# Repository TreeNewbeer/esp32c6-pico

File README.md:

# ESP32-C6 Pico · Rev A

2026-09-11 第一版 PCB 提交快照：保留用户在居中后对 R19、R15、局部短线及图形的继续调整；R19 / R15 当前坐标为 (115.70, 120.40) / (115.70, 122.36) mm。已重新填铜并同步贴装坐标、二维预览和报告，**ERC 0、DRC 错误 0 / 丝印警告 1、未连接 0、一致性问题 0，QA 39/53**。见 [当前提交记录](output/first-pcb-revision.json)。以下居中对比及旧 3D 图保留为历史记录。

2026-09-10 最新 PCB 微调：以用户已基本完成的第一版 layout 为输入，USB 向右 1.00 mm、两颗按键各向右 0.50 mm，均对齐板框中心 X=110.00 mm；按键间距及纵向位置不变，RST / BOOT 文字跟随移动，D2 位号丝印隐藏。为避让孔位及器件庭院，D4 向右 0.20 mm / 向下 0.10 mm、R15 向右 0.50 mm，局部修整短线；其余器件位置及板框、射频、晶振、禁布区不变。原理图和电路网络未改动，过孔仍为 89 个。重新填铜后 **ERC 0、DRC 错误 0、未连接 0、一致性 0**，保留输入已有的 1 项板头丝印警告；**QA 39/53，无新增失败项**。贴装坐标、二维预览和当前原理图导出的网表已更新，旧 3D 图为历史记录。见 [修改记录](output/usb-buttons-centered.json) 与 [前后对比](output/usb-buttons-centered-comparison.png)；以下先前轮次的数据仅作历史参考。

2026-09-10 最新（仅原理图）：RGB 控制已由 GPIO21 切回 **GPIO8（U1.14，与 J2.7 共用）**，GPIO21（U1.34）标记不连接。已按用户确认对齐官方 DevKitC-1 v1.4：**R9 = 3.3 kΩ 将 GPIO8 上拉到 3.3 V，R19 = 10 kΩ 将二极管阳极侧数据节点上拉到 5 V，R15 = 0 Ω 串联接入 DIN**。保留两颗上拉，D6 阴极朝 GPIO8；R9 / R15 的阻值、BOM 和检查条件均已同步。ERC 0，主控外围实线检查全部通过。PCB、布局和贴装坐标未修改，尚未同步这次 GPIO8 变更；既有 DRC / QA 报告不是新原理图的一致性验证。最新网表、BOM 和两页预览已更新；设计清单同时修正输入原理图已有的 J3 脚序及 D2 封装字段偏差，未改动这些电路。见 [GPIO8 原理图记录](output/rgb-gpio8-schematic.json) 与 [RGB 局部预览](output/schematic/rgb-gpio8.png)。

以下布局轮次和检查数字为历史记录；当前原理图与 PCB 的同步状态以上述说明为准。

当前 PCB 为 **18.0 × 29.0 mm、四层、标称 0.8 mm**，使用 ESP32-C6 QFN40、4 MB 外置 Flash、横向陶瓷天线与原生 USB Serial/JTAG。已按最新原理图移除 USB 的 R12、R13、C27、C28 并完成 USB 直连布线；RGB 灯改用二极管加 5 V 上拉驱动，不再使用电平转换芯片。

2026-09-10 此前 RGB 驱动同步：**按官方 ESP32-C6-DevKitC-1 v1.4 的方式，用 D6（1N4148WS / SOD-323）+ R19（10 kΩ 上拉到 USB 5 V）替换 SN74LV1T125 电平转换器**，删除 U4、其去耦 C26 和 GPIO21 下拉 R16；R15 = 330 Ω 移到 D2 的 DIN 焊盘旁，原来绕过 D2 的数据绕线一并删除。庭院净省约 10 mm²，背面原缓冲器口袋基本腾空，少一个 IC 料号。电平按二极管压降核算（高电平约 3.9 V > 0.7 × VDD，低电平约 0.7 V < 0.3 × VDD，10 kΩ 上拉上升沿约 105 ns），**尚未上电或用示波器实测**。范围、基线对比与哈希见 [RGB 二极管驱动记录](output/rgb-diode-drive.json)，局部对比见 [改动前后对比图](output/rgb-diode-comparison.png)。

2026-09-10 此前 USB 同步：**删除 R12 / R13（22 Ω 串阻）和 C27 / C28（选装电容）**，U1.18 / U1.19 直接连接 USB_D− / USB_D+；保留 USB-C、CC 下拉及 D4 静电保护。清除两条电容支路及其过孔，简化主控附近走线；保持 0.15 mm 线宽、每根数据线两次换层，不增加蛇形补偿。

当前 **59 个器件位、55 个默认装配；ERC 0、原理图一致性 0**。PCB 仍处在重排右排针（J3）的过程中，**DRC 5 项违规、9 项未连接、QA 45/53**：既有的 MCU 7/9 个中心地孔两项检查、匹配网络共轴、天线/晶振间距，加上尚未连上的 7 条 J3 网络、3 个未盖油过孔和 R14 旁一处 +3V3 间距。这些项与 RGB 改动前的同一工程基线（DRC 5、未连接 9、QA 44/52）逐项一致，本轮没有新增违规，但**投板前必须先完成 J3 布线并清零**。除本轮 RGB 三件外，其余器件的位置、角度、安装面和封装不变；BOM、坐标、原理图和 PCB 预览已更新，详见 [RGB 二极管驱动记录](output/rgb-diode-drive.json) 与 [USB 同步记录](output/usb-layout-sync.json)。尚未进行实板 USB、RGB 或射频验证。

以下引脚同步及布局调整记录为历史状态；当前器件数、USB 与 RGB 电路以上面两段为准。

2026-09-10 此前引脚同步：**J2 / J3 全部 24 个脚位已按用户修改的原理图更新，信号、电源和接地均已连通，包括 GPIO5（U1.11 → J2.4）**。左列从板头依次为 GPIO2–GPIO11、3V3、GND；右列为 GPIO1、GPIO0、GPIO15、TX、RX、GPIO18、GPIO19、GPIO20、GPIO22、GPIO23、5V、GND。背面功能丝印、设计清单、原理图预览及 PCB 预览已同步。

**全部 64 个器件的位置、角度、安装面、封装和装配状态均保持输入状态**；板框、logo、禁布区，以及 RF、晶振、USB、Flash 等非排针网络的原有铜线几何保持不变。重排排针支路，同时接回输入板已断开的 C8/C9/C10 3V3 支路，恢复 64 个器件的原理图关联路径。为分隔的表层地铜补充四颗接地过孔，Y1.2 最近地孔距离改善为 0.65 mm；另将一颗原有 VBUS_USB 过孔明确设置为双面盖油。过孔从本次实际输入的 122 颗变为 130 颗。

当前 **ERC 0、DRC 违规 0、未连接 0、原理图一致性 0；独立 QA 48/52**。没有新增失败项；保留四项既有失败：MCU 中心地孔仍为 7/9（两项检查）、天线匹配器件共轴及天线/晶振 8.5 mm 间距目标。最新报告与输入基线见 [引脚同步记录](output/pin-layout-sync.json)；尚未进行实板或射频验证。以下收窄记录属于本轮之前的历史状态，旧脚位和 GPIO5 待连状态以本段及下方接口表为准。

2026-09-10 左侧收窄：板框现为 **18.0 × 29.0 mm**，左板边与 J2 同步右移 **2.00 mm（四个 0.50 mm 步长）**，面积由 580 降至 522 mm²，减少 10%。J2 / J3 中心 X 为 102.25 / 117.75 mm，列中心距 15.50 mm；针距仍为 2.00 mm，焊盘铜到两侧板边仍各 0.575 mm。为避让左排针，仅另调整背面的 C8、C28、R8，其他 60 个器件保持位置、安装面和封装，L2、RF/晶振走线及 USB 数据主干保持不动。J2 第 4 / 5 脚改为 GPIO2 / GPIO1，原理图、设计清单及背面丝印已同步。

历史收窄轮次的待连状态（本轮已完成）：**当时按用户要求保留 GPIO5，U1.11 → J2.8。** U1 焊盘中心为 (106.5625, 115.20) mm，J2 焊盘中心为 (102.25, 128.00) mm；该网络已清除未完成的线头，打开 KiCad 后可直接按飞线补接，信号宽度为 0.15 mm，In1.Cu 继续留作 GND。当前 **ERC 0、DRC 违规 0、原理图一致性 0、未连接 1；QA 45/52**。QA 保留原有六项失败，新增的一项失败就是这条明确预留的连接，未放宽检查。总过孔由 125 减至 124。完成 GPIO5 后须重填铜并重新运行 DRC / QA；当前不是已全部布线的生产文件。范围、备份与端点见 [18 mm 收窄记录](output/width-18mm.json)。

2026-09-09 历史 L2 调整：**L2（2 nH、0402）移至 B.Cu**，从 (102.10, 113.00) mm 移到 (111.55, 112.65) mm，腾出正面左排针旁的原占位。其余 63 个器件、全部信号线、板框、禁布区和两个 logo 均保持输入状态；C11/C19/C20 保持正面。只调整 +3V3 / V3A 的局部连接，移除原输入过孔，新增一颗双面盖油的输出过孔，总数仍为 125。到 U1 两个供电脚的路径约 3.7–3.9 mm（含标称 0.8 mm 过孔贯穿长度）。填铜后 **DRC 0、未连接 0、一致性 0；QA 46/52**，较本次实际输入的 45/51 新增一项通过检查，原有六项失败不变。BOM 器件信息不变，装配坐标和正反面预览已同步；射频与供电表现尚未实测。该轮范围、备份和验证见 [L2 迁移记录](output/l2-back-migration.json)，后文各轮数字保留为历史记录。

2026-09-09 封装替换：**U3 改为 W25Q32JVSNIQ、150 mil SOIC-8（3.9 × 4.9 mm 本体）**；**D5 改为 at820_tiga 的 BAT760-7 / SOD-323**，保持防反灌方向。U3 向左 0.20 mm、向板头 0.10 mm，C6 向右 0.10 mm，D5 中心不动；其余 62 个器件的封装、位置和安装面不变。板框、射频、晶振和 USB 数据线几何保持不变。SOIC 引脚焊盘较长，占位略增；D5 庭院占位约减少 39%，本轮没有缩小板框。

本轮已重新导出网表、ERC、填铜、DRC 和独立 QA：**ERC 0、DRC 0、未连接 0、一致性 0；QA 45/51**，无新增失败项。修改前实际文件重新检查为 43/49，保留 MCU 接地孔数量、匹配网络共轴、天线/晶振间距、晶振接地孔距离、MCU 散热孔清单及一颗普通过孔未显式双面盖油六项既有失败。SOIC-8 没有中心焊盘，工艺目标改为仅 U1 的 9 孔，当前实有 7 孔；没有降低 U1 的要求。具体变更、哈希与基线见 [封装替换记录](output/package-changes.json)。

**F1 已按用户要求删除**：原理图和 PCB 均移除 1206 自恢复保险丝，USB 的 `VBUS_USB` 直接连接 D5 阳极，取消 `VBUS_FUSED` 网络。移除绕到板尾 F1 的走线，保留 D5 防反灌；其余 64 个器件的位置、安装面和封装不变。BOM、装配坐标及预览已同步，默认装配由 59 个减为 58 个。删除后的 ERC、DRC、未连接和原理图一致性均为 0；QA 仍为 45/51，六项既有失败不变。删除 F1 时的检查结果为历史记录，最新结果见上方引脚同步记录。

2026-09-09 历史原理图复核：已对照 `docs/` 的 WROOM-1 / WROOM-1U 模组图，将晶振串联器件 **L4 = 24 nH 更正为 R18 = 0 Ω、0402 电阻**，对应模组图的 R4；原理图符号、PCB 封装、BOM 和检查条件均已同步。另记录 VDDA3P3、VDDA1/VDDA2 的本地去耦差异。重新填铜后，ERC 0 项、原理图一致性 0 项、未连接 0 项；DRC 仍有原有 2 项，独立 QA **43/48 通过**。详细依据与风险见 [外围电路复核](docs/ESP32_C6_SCHEMATIC_REVIEW.md)。下文跳过 QA 的描述属于此前布局轮次。

天线本体在板头右侧横向放置，末端铜箔向左展开、保持开路；板头全层不铺铜区域为 **18.0 × 3.8 mm**。AE1 馈电焊盘与 R6 对齐，正面馈线直接向下连接，不再从匹配网络折返向左。Codex 图标移至左侧；Flash U3、USB TVS D4 和排针位于背面，两颗按键位于正面。

六颗 Flash 串联电阻 R17、R1–R5 已改为 0402，在背面排成一行，中心间距 1.20 mm。Flash U3 与 TVS D4 各向 USB 方向移动 0.80 mm，为焊盘外过孔和这排电阻留出空间；板框不变。C7 在主控 VDD_SPI 扇出旁的正面，C13 位于 3.3V 供电脚附近，保留短去耦连接。RGB 驱动改为二极管电平转换后，D6 占用背面原缓冲器位置，R19、R15 移到 D2 右侧的正面空位，DIN 与数据节点的绕行走线随之删除。排针功能标注统一保留在背面，正面左侧的重复标注已清除。

2026-09-09 历史板宽调整：在天线右移后的 20.5 × 29 mm 版上，将左右板边各收窄 **0.25 mm**，当前板框为 **20 × 29 mm**，面积从 594.5 mm² 降至 **580.0 mm²（减少约 2.44%）**。两列排针位置与 18.10 mm 列间距保持不动，焊盘外缘距两侧板边均为 **0.275 mm**，满足当前 0.25 mm 规则。器件、过孔及走线几何保持输入版本。贴装坐标原点同步更新到新板框左下角 (99.00, 137.50) mm。

2026-09-09 排针内移：板框保持 **20 × 29 mm**，J2 向右、J3 向左各移动 **0.30 mm**，两列中心距由 18.10 mm 改为 **17.50 mm**。J2 / J3 中心 X 分别为 100.25 / 117.75 mm，针距 2.00 mm、脚号与网络顺序不变。焊盘铜外缘距左右侧边各 **0.575 mm**；按封装标称 2.00 mm 宽塑料座计算，本体距侧边各 **0.25 mm**。背面引脚标注及相关局部走线已同步调整，最新预览与装配坐标位于 `output/`。

重新填铜后，**DRC 0 项、未连接 0 项、原理图一致性 0 项**；独立 QA **44/49 通过**，新增的排针边距检查通过，其余五项失败均在修改前存在。旧 `output/qa.json` 的 PCB 哈希与输入文件不符，因此已对原始备份重新建立基线（43/48），未沿用旧报告中的两项孔距违规。当前剩余项为 MCU 接地孔数量、天线匹配器件共轴、天线/晶振间距、晶振接地过孔距离及 11 个散热孔清单。范围与基线对照见 [排针内移检查记录](output/headers-inward.json)。

天线与晶振名义本体边缘最近距离约 **5.070 mm**，低于历史 8.5 mm 项目几何目标；与本次输入 PCB 一致。该历史门槛保持不变，当前独立 QA 据此报告失败。射频和晶振信号仍在正面且不换层，晶振规则区保留；3.8 mm 净空及右侧天线布局尚需实板射频验证。

正面天线旁原 `2.4 GHz` / `NO COPPER` 丝印替换为 **Codex 图标**；背面加入用户个人 logo 的单色人物图形，并将 `REV A` 移到旁边。两个 logo 都是可编辑丝印图形组，背面按正常观看方向镜像放置。原图、SVG、来源和尺寸记录见 [docs/logo/README.md](docs/logo/README.md)。

直接用 KiCad 10 打开 `esp32-c6-pico.kicad_pro`。如编辑器仍显示修改前的内容，请关闭旧窗口并重新打开磁盘文件，避免旧窗口覆盖新文件。

当前封装约定：**射频匹配的 6 个电阻/电容保持 0201，其余全部 35 个电阻/电容统一 0402**，包括 C19、C20、C23 等大容量电源电容及 Flash 串阻。容量、阻值、网络和 DNP 状态保持不变。大容量电源电容保留最低 10V 额定耐压要求，实际料号与偏压下的有效容量仍需核对。变更清单见 [POWER_PASSIVES.md](POWER_PASSIVES.md) 和 [全部阻容封装表](output/passive-packages.csv)。

主原理图已把 ESP32-C6 的供电去耦、上电复位、BOOT、晶振、Flash、USB 直连引出、UART 与 RGB 驱动沿芯片引脚用实线连接。电源输入、USB 接口与排针位于第二页。USB 数据引脚已与第二页的同名数据网络直接连接。

此前尝试了 **18 × 30 mm**：目标尺寸的器件摆放可以容纳，但布线候选仍有 18 处未连接，该轮主工程保留了 20.5 × 32.5 mm，后续从板头收短到 32.0 mm。此前候选、剩余问题和原始检查结果见 [SHRINK_TRIAL.md](SHRINK_TRIAL.md)。

## 已完成的电路

- USB-C 正反插数据连接、CC1/CC2 独立 5.1 kΩ 下拉、USBLC6-2SC6 静电保护；数据线直接连接主控，已删除 22 Ω 串联电阻及选装 EMI 电容。
- AP2112K-3.3 稳压、输入保护、肖特基防反灌、主电源及各供电脚的去耦；RF 电源使用独立 LC 滤波。
- CHIP_EN 的 10 kΩ / 1 µF 上电延时，RESET、BOOT 按键，GPIO8/9 上拉与 UART0 备用下载接口。
- W25Q32JVSNIQ、SOIC-8 150 mil 外置 Flash，真正接通 VDD_SPI；40 MHz / 8 pF 晶振，两个外壳脚接地，并保留负载调试与 R18 = 0 Ω 串联电阻。
- 芯片端 CLCCL 射频网络、天线端 π 网络、低电容 ESD 选装位，以及陶瓷天线开路端调谐铜箔。
- WS2812B-2020 RGB 灯：原理图改由 GPIO8 经 D6（1N4148WS）与 R19（10 kΩ 上拉到 USB 5 V）驱动，R9 = 3.3 kΩ 保留 GPIO8 的 3.3 V 上拉，R15 = 0 Ω 接入 DIN，控制引脚和三个电阻值已按官方 v1.4 对齐；PCB 待用户同步。

## 检查与交付文件

当前原理图 ERC 0、实线检查通过，见 `output/rgb-gpio8-schematic.json`。PCB 尚未同步本次 GPIO8 变更；`output/drc-final.json` 和 `output/qa.json` 保留此前布局结果，下文各日期记录保留当时状态。

2026-09-09 历史排针内移轮次使用 KiCad 10.0.6 重新填铜并检查：**DRC 0 项、未连接 0 项、原理图一致性 0 项；独立 QA 44/49 通过，无新增失败项**。本轮未修改原理图，既有 ERC 报告为 0 项。当前报告为 `output/drc-final.json`、`output/qa.json` 和 `output/headers-inward.json`；`output/layout-20x29mm.json` 及此前两项孔距违规的记录属于历史轮次。

原先 65 项一致性报错来自 PCB 器件字段缺失。现已按原理图为 65 个器件同步 141 处字段，包括 MPN、AssemblyNote 和 Datasheet；新增字段隐藏显示，保留封装库自带的额外字段。原理图、网络连接、封装、器件值和 DNP 状态保持不变。已重新填铜，并在重新加载磁盘 PCB 后启用 `--schematic-parity` 验证为 0 项；QA 新增逐字段比较与一致性报告检查，后续 DRC 命令也必须带此参数。

USB 保持简洁路径，没有加入蛇形等长补偿。两根线在按键上方换到底层，经过靠近连接器的 TVS，再换回正面连接 USB-C 焊盘。接受自然扇出带来的少量长度差；QA 长度统计区分铜层，并计入标称过孔贯穿长度。

全板信号走线统一为 **0.15 mm**（含 USB、射频、晶振及芯片扇出），非 GND 电源走线统一为 **0.20 mm**；GND 保留原有线宽。`Power` 网络类覆盖 `+3V3`、`+5V`、`V3A`、`VBUS_USB`、`VDD_SPI`，其他信号使用 `Default`。自定义规则同时限制最小和最大线宽，独立 QA 核对每段走线与实际网络类；相关局部路径已按新宽度调整。线宽统一不代表阻抗或载流能力已经实测达标。

外围焊盘内的过孔已改为焊盘外短线扇出，并检查正反面的阻焊开窗；孔边间距至少 0.10 mm。当前仅允许 U1 中心接地焊盘的 9 个填孔盖铜过孔，实际清单为 7 个；SOIC-8 U3 无中心焊盘。为腾出局部扇出空间，调整了 C7、C11、R2、R3、R7 的位置；同批调整的 C27、R16 已在后续 USB 与 RGB 简化中删除。

| 文件 | 用途 |
| --- | --- |
| `esp32-c6-pico.kicad_sch` / `power-io.kicad_sch` | 两张可编辑原理图 |
| `esp32-c6-pico.kicad_pcb` | 已布线 PCB，含叠层和禁布区 |
| `esp32-c6-pico.kicad_dru` | 固定线宽、焊盘孔距与晶振下方的非接地过孔禁布规则 |
| `output/pcb-front.svg` / `pcb-back.svg` | 正反面布线预览 |
| `output/rgb-diode-drive.json` | RGB 二极管电平转换的改动范围、基线对比与验证 |
| `output/rgb-diode-comparison.png` / `.svg` | RGB 驱动改动前后的正反面局部对比 |
| `output/pin-layout-sync.json` | 最新排针引脚、完整布线、位置保护、输入基线及验证 |
| `output/width-18mm.json` | 历史 18 mm 收窄、当时 GPIO 换序与待连线记录 |
| `output/l2-back-migration.json` | L2 背面迁移范围、备份、连通性及检查基线 |
| `output/package-changes.json` | 历史封装替换范围、尺寸、网表与检查基线 |
| `output/headers-inward.json` | 历史排针内移的尺寸、修改范围及检查基线 |
| `output/width-20mm-comparison.png` / `.svg` | 历史 20.5 → 20.0 mm 板宽对比 |
| `output/antenna-right-29mm-comparison.png` / `.svg` | 历史 28 → 29 mm 与天线右移对比 |
| `output/antenna-28mm-comparison.png` / `.svg` | 历史 32 → 28 mm 压缩对比 |
| `output/antenna-layout-comparison.png` / `.svg` | 此前天线末端铜箔调整的历史对比 |
| `output/usb-routing-comparison.png` / `.svg` | 此前删除 USB 蛇形的历史局部对比 |
| `output/layout-repack-comparison.png` / `.svg` | 此前换面布局及缩短板框的历史对比 |
| `output/crystal-isolation-comparison.png` / `.svg` | 此前天线前移并加长板框的历史对比 |
| `output/crystal-down-headers-comparison.png` / `.svg` | 此前晶振下移、排针换面与尺寸调整对比 |
| `output/board-3d-top.png` / `board-3d-bottom.png` | 含最新 logo 的正反面 3D 布局预览 |
| `docs/logo/` | 个人原图、两面丝印 SVG、图形来源和放置参数 |
| `output/assembly-front.svg` / `assembly-back.svg` | 带位号的装配视图 |
| `POWER_PASSIVES.md` / `output/power-passives.csv` | 当前 0402 约定、封装变更记录和选料说明 |
| `output/passive-packages.csv` | 全部 40 个电阻/电容及累计 12 个封装变化记录 |
| `output/bom.csv` | BOM；`Populate=NO` 表示不装 |
| `output/placement.csv` | 双面贴装坐标，已排除 DNP；坐标原点为板左下角 |
| `output/via-in-pad.csv` | 当前 7 个 MCU 散热焊盘内孔，尚未满足 9 孔目标；须填孔盖铜 |
| `FABRICATION.md` | 必须确认的工艺、阻抗与样板验证项目 |

板上共 59 个器件位，默认装配 55 个。默认不装 D1、L3、C17、C18。3D 图为布局示意，部分标准库封装缺少 3D 模型；器件是否装配以 BOM 和二维装配图为准。

## 接口与下载

**从正面看**，USB 朝下、天线朝上时，J2 在左、J3 在右，两列 1 脚均靠近天线；从背面观察时左右对调，编号不倒序。排针塑料座和长针在背面，正面为焊接端。针距为 **2.00 mm**，两列中心距为 **15.50 mm**；这些尺寸不能按 2.54 mm 面包板间距处理。

| 脚号 | J2（左列） | J3（右列） |
| --- | --- | --- |
| 1 | GPIO2 | GPIO1 |
| 2 | GPIO3 | GPIO0 |
| 3 | GPIO4 | GPIO15 |
| 4 | GPIO5 | UART0 TX / GPIO16 |
| 5 | GPIO6 | UART0 RX / GPIO17 |
| 6 | GPIO7 | GPIO18 |
| 7 | GPIO8 | GPIO19 |
| 8 | GPIO9 / BOOT | GPIO20 |
| 9 | GPIO10 | GPIO22 |
| 10 | GPIO11 | GPIO23 |
| 11 | 3V3 输出 | 5V 输出* |
| 12 | GND | GND |

*5V 引脚实际电压等于 USB 电压扣除 D5 压降，不是精密 5.00 V。USB 电源直接经 D5 给稳压器和 5V 引脚供电，板上不再设置自恢复保险丝；RGB 灯与其 10 kΩ 上拉接 USB 原始电源。3V3/5V 引脚按电源输出使用，不要在连接 USB 时再向这些引脚注入外部电源。所有 GPIO 为 3.3 V 逻辑。

USB 下载使用芯片内置 USB Serial/JTAG（GPIO12=D-，GPIO13=D+）。需要手动进入下载模式时：按住 BOOT，点按 RESET，再松开 BOOT。UART0 备用下载时，使用 3.3 V 电平的串口适配器，交叉连接 TX/RX 并共地。GPIO4、5、8、9、15 是启动配置脚，外接电路不能在复位时强制成错误电平。

## 设计边界

这是一版用于验证的样板设计，尚未进行上电、测温或射频实测。横向天线、轴向开路端铜箔、18.0 × 3.8 mm 净空和缩短后的地平面均属于本工程的样板选择；3.8 mm 不是厂商保证的最小净空，原参考板的增益、带宽和方向图不能直接套用。匹配、效率和通信表现需在实际板卡及外壳中验证。

射频匹配、晶振负载与名义阻抗均需结合实际叠层、装配和外壳确认。U1 的中心散热焊盘内孔须填孔盖铜，当前 7 孔尚未满足 9 孔目标，普通盖油不能替代；具体工艺与实板验证要求见 `FABRICATION.md`。

`tools/` 保留了设计过程与验证脚本。`verify_design.py` 可重跑网络与规则核对；布局生成和布线脚本会重建或修改 PCB，不能当成对最终布线无损的更新命令。

## 依据

- [Espressif ESP32-C6 原理图设计指南](https://docs.espressif.com/projects/esp-hardware-design-guidelines/zh_CN/latest/esp32c6/schematic-checklist.html)：供电、启动配置、晶振、USB 与射频匹配。
- [Espressif ESP32-C6 PCB 布局指南](https://docs.espressif.com/projects/esp-hardware-design-guidelines/zh_CN/latest/esp32c6/pcb-layout-design.html)：接地参考层、芯片底部接地、射频与时钟路径。
- 工程内 `docs/C127611_CAA3DCCF3A021118096CAD99FC50242A.pdf`，Walsin `ASC_RFANT5220110A0T_V13` 第 3–4 页：天线焊盘、开路端铜箔与测试板几何。
- [Eaton E9X 数据手册](https://www.eaton.com/content/dam/eaton/products/electronic-components/resources/data-sheet/eaton-e9x-crystal-resonator-mhz-data-sheet-elx1389-en.pdf)：Y1 的频率、负载、电气规格与引脚。
- [Diodes 1N4148WS 数据手册](https://www.diodes.com/assets/Datasheets/1N4148WS_BAV16WS.pdf)：RGB 数据电平转换二极管，SOD-323、VF ≤ 0.715 V @ 1 mA、CT ≤ 2 pF。
- 工程内 `docs/esp32-c6-devkitc-1-schematics_v1.4.pdf` 第 2 页：官方 RGB 驱动使用 D11（1N4148W）+ R29（10 kΩ 上拉到 VCC_5V）+ R17（0 Ω），本板据此改用同一结构。
- [Nexperia PESD5V0F1BL-Q 数据手册](https://assets.nexperia.com/documents/data-sheet/PESD5V0F1BL-Q.pdf)：低电容天线 ESD 选装器件。

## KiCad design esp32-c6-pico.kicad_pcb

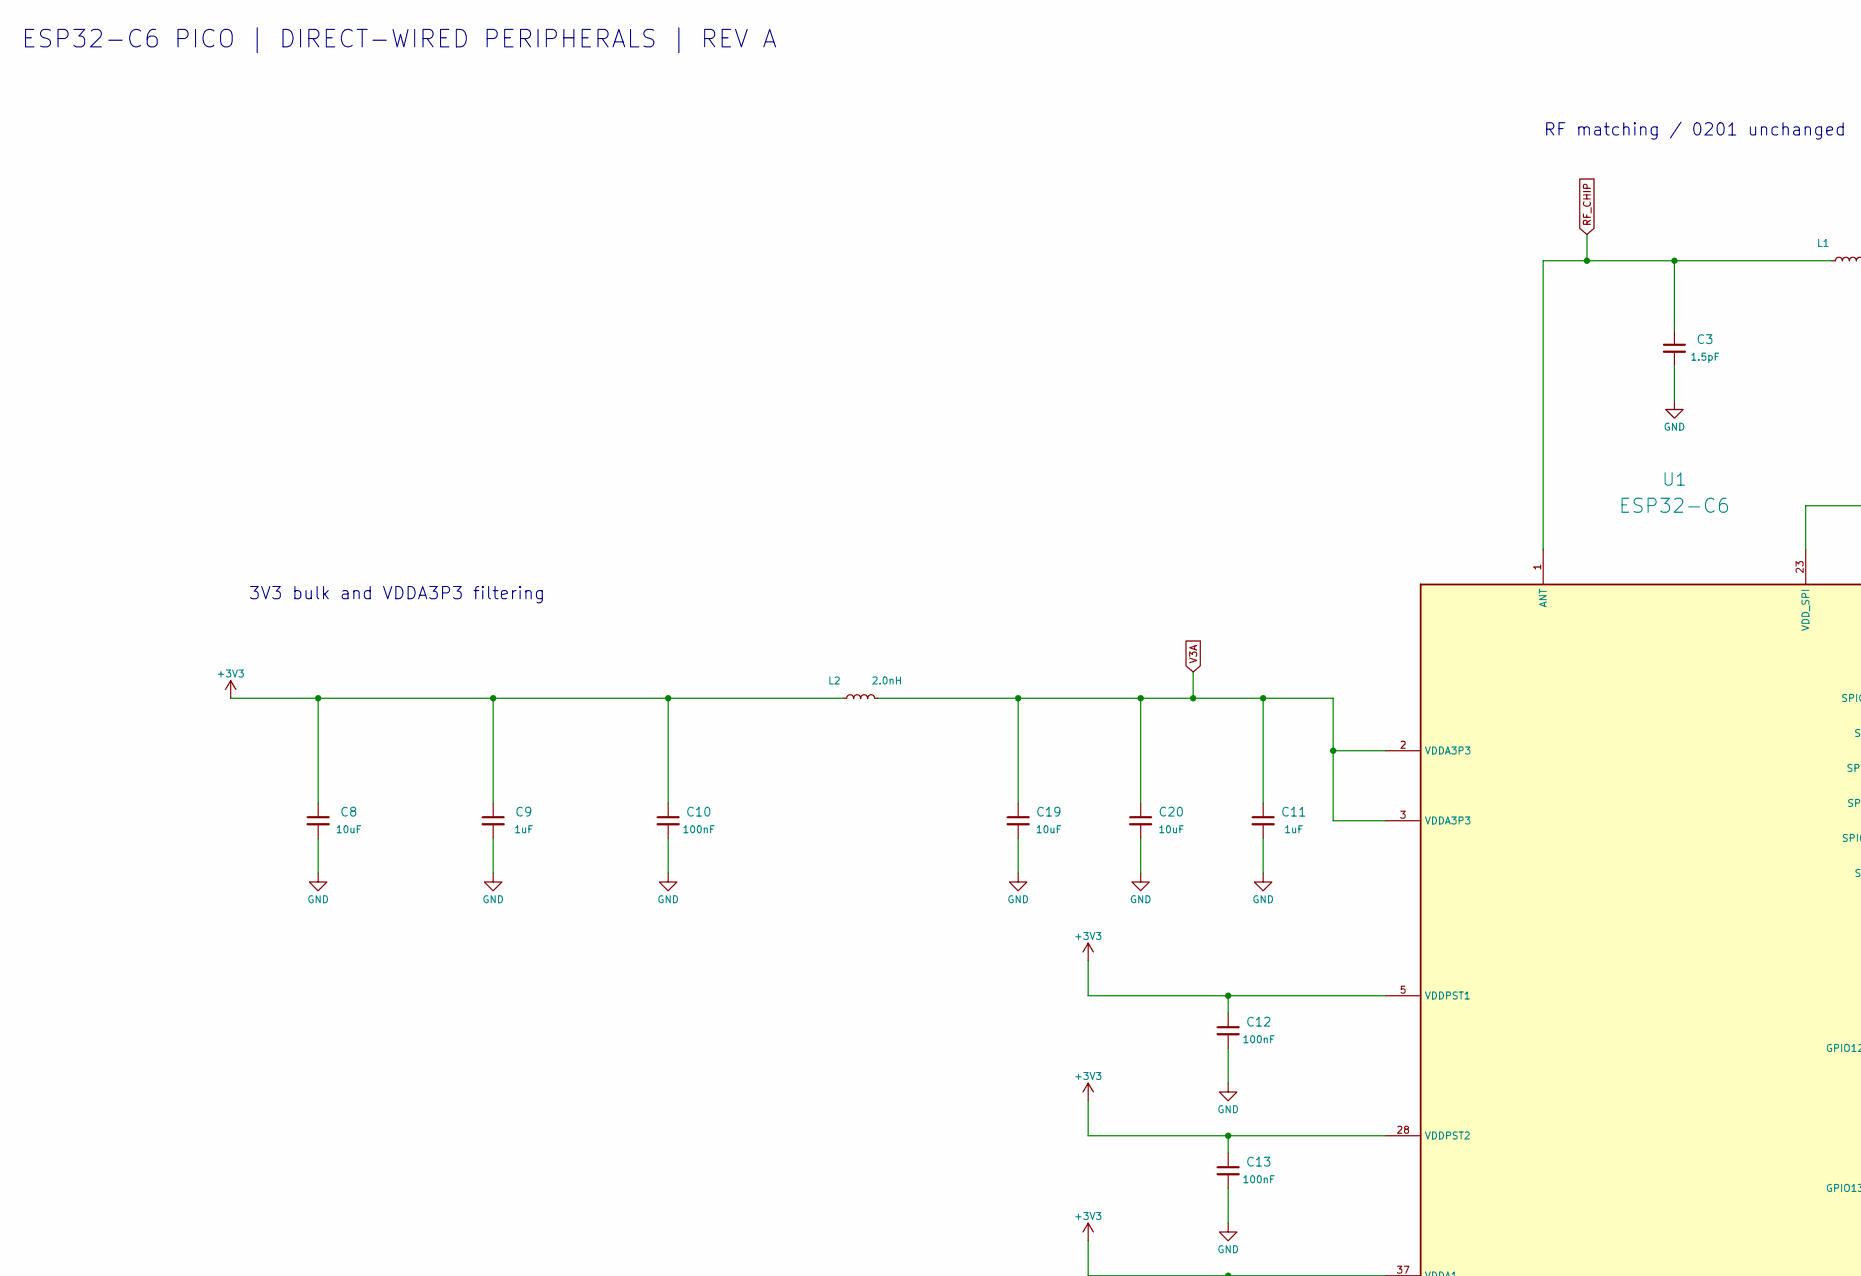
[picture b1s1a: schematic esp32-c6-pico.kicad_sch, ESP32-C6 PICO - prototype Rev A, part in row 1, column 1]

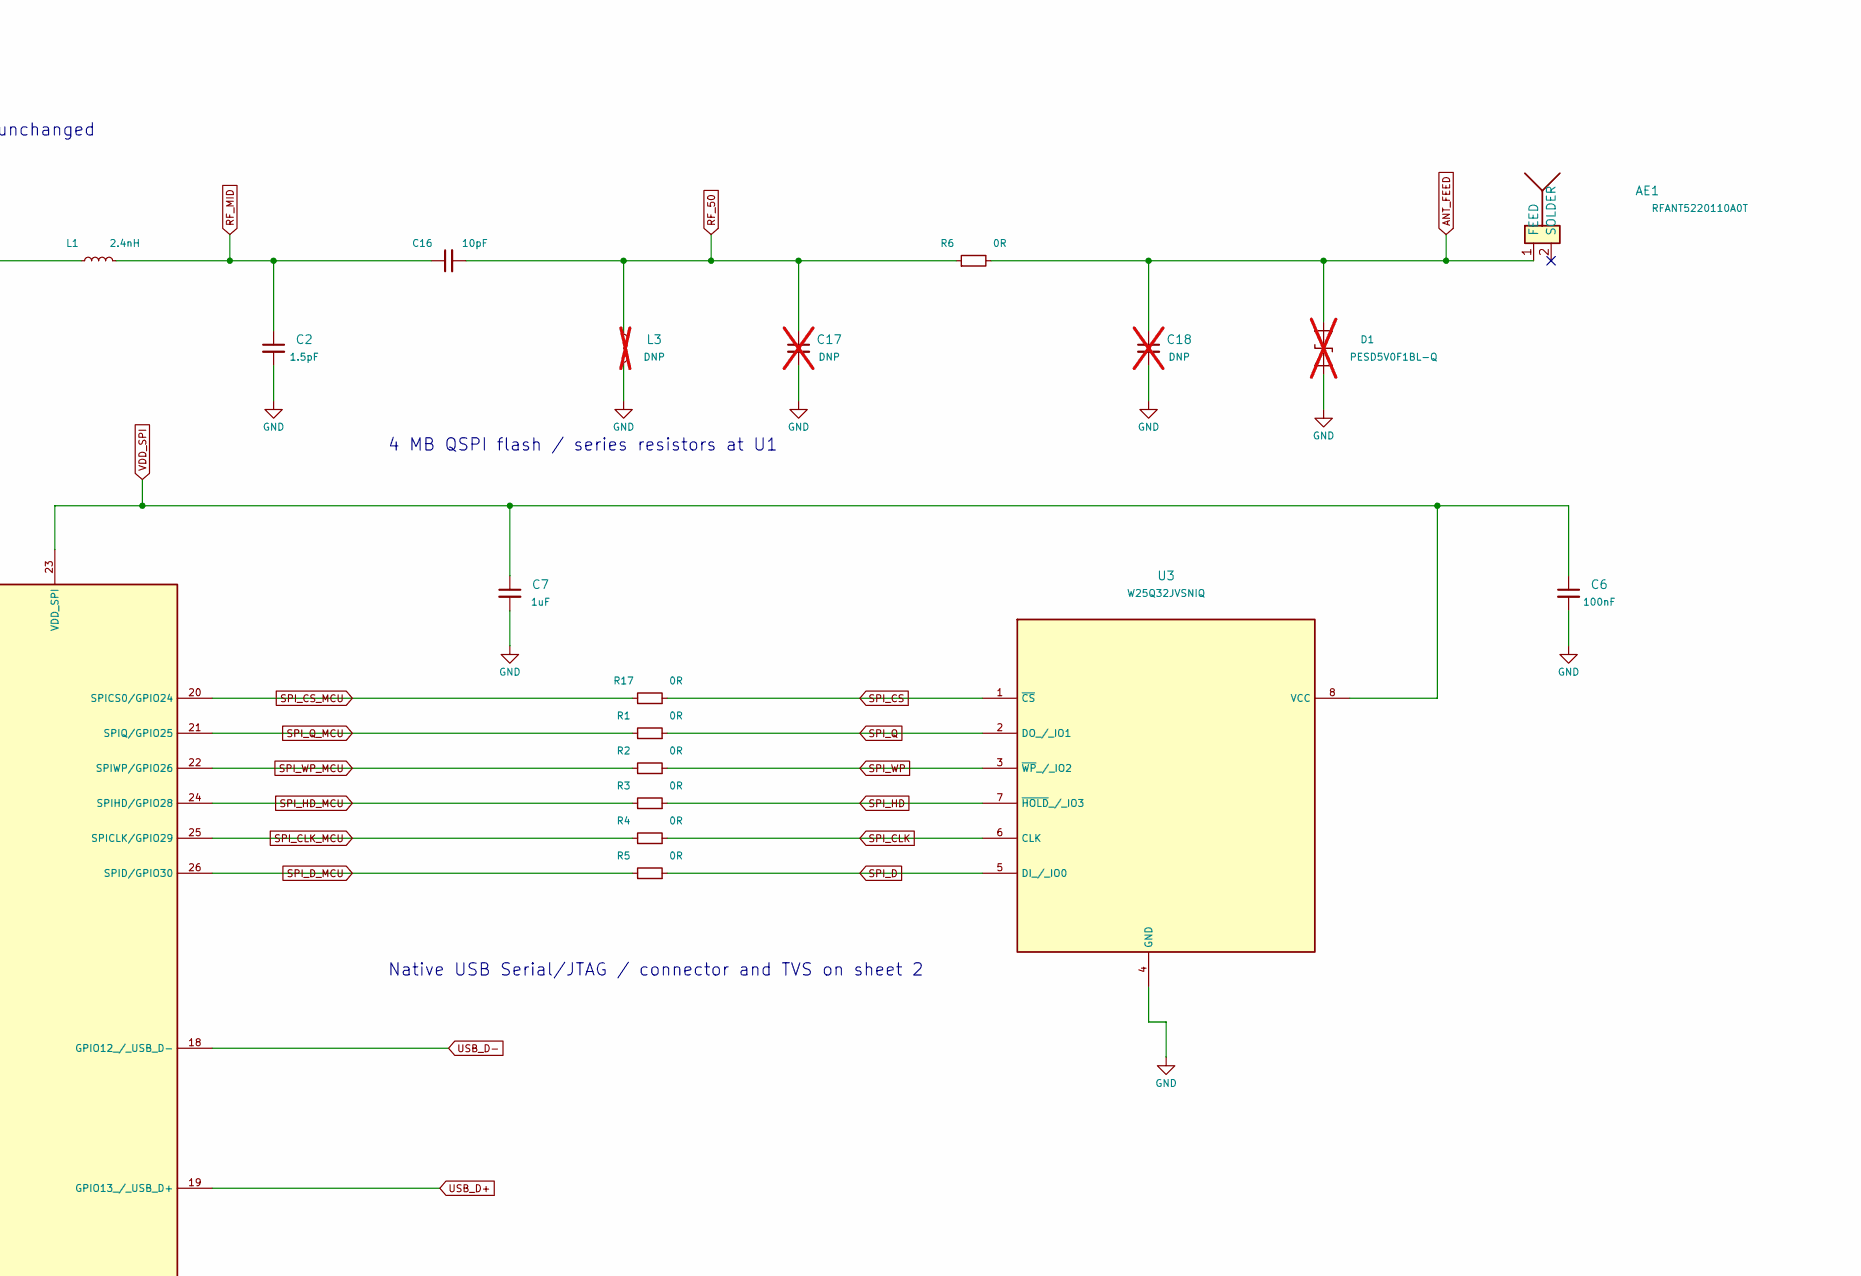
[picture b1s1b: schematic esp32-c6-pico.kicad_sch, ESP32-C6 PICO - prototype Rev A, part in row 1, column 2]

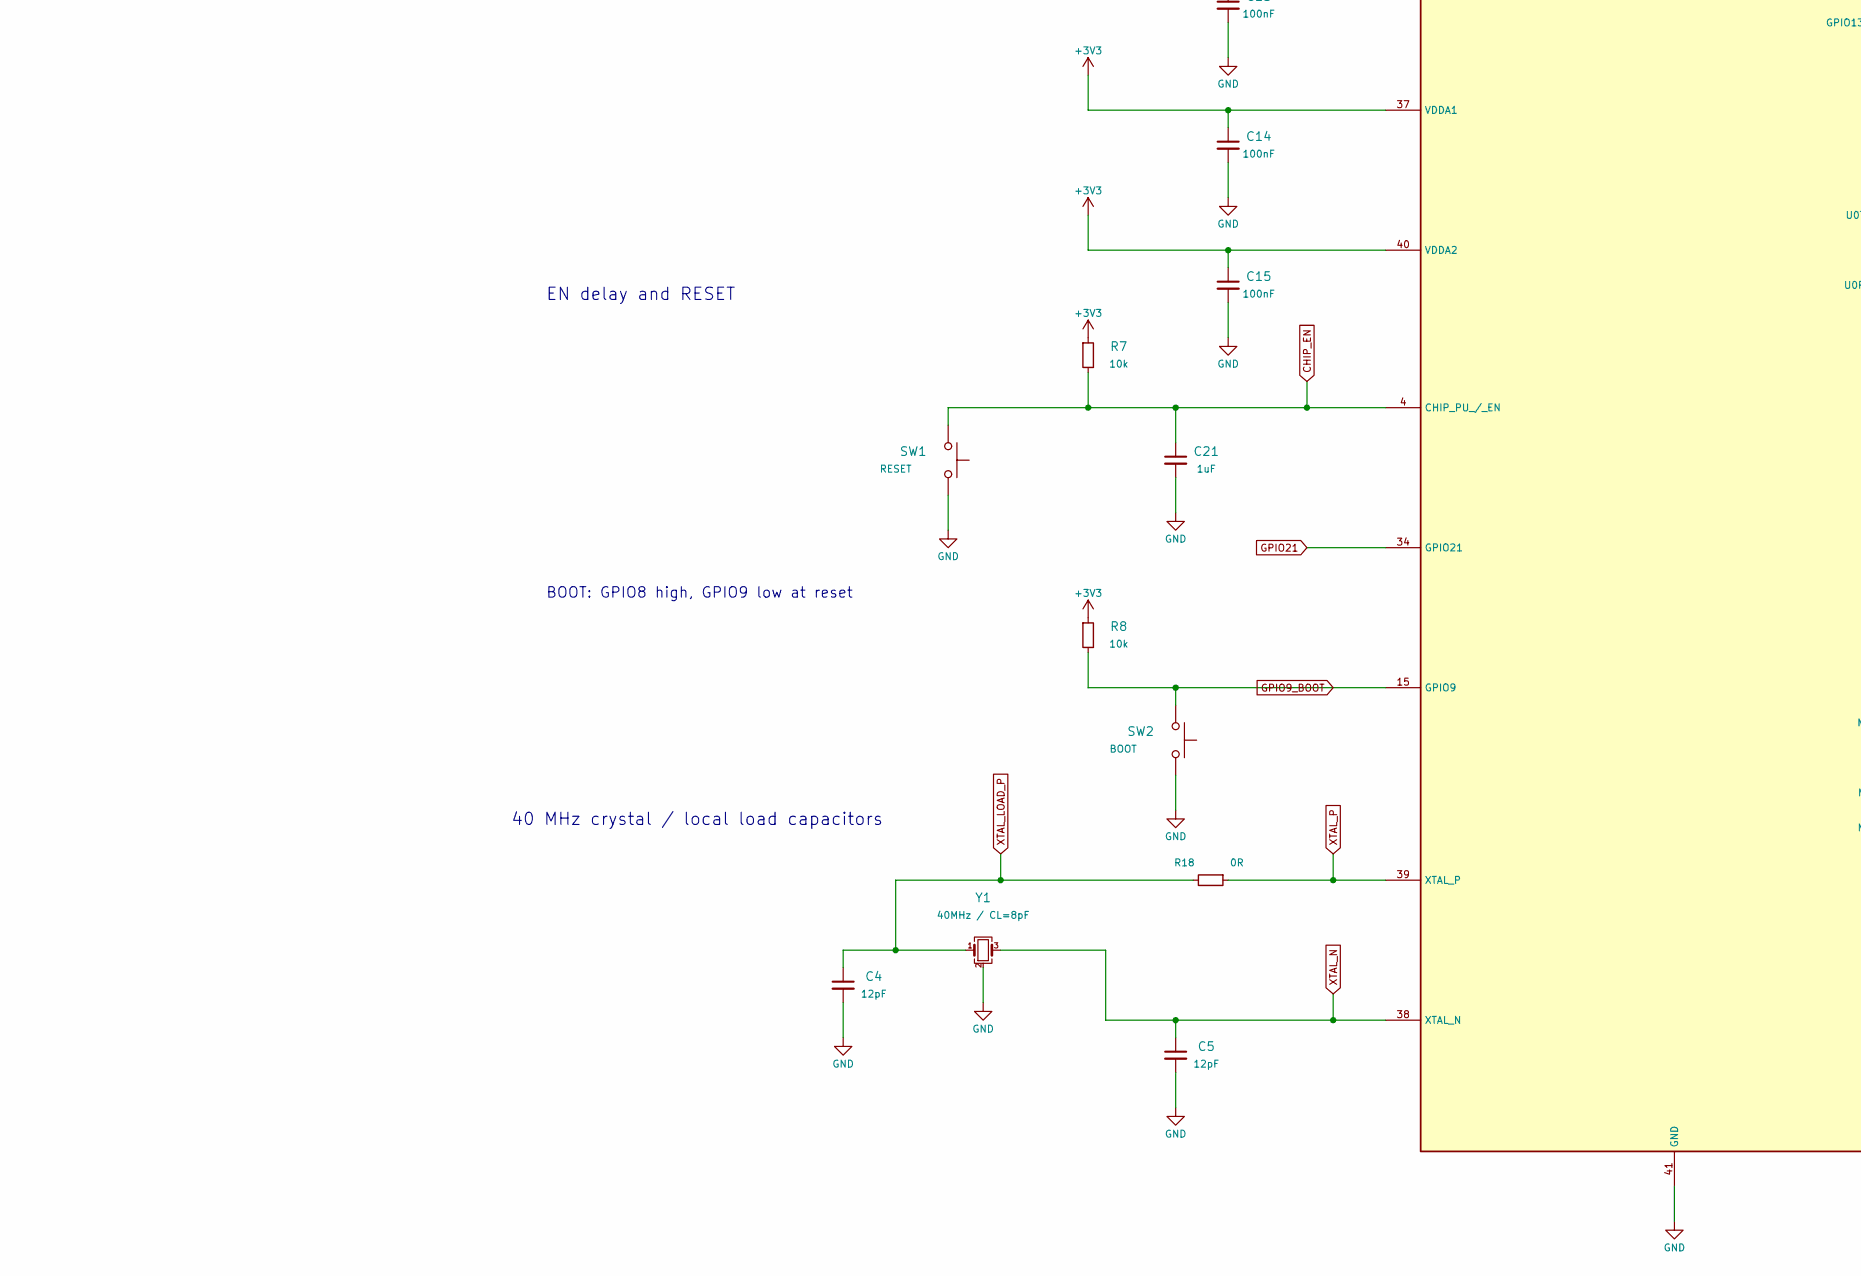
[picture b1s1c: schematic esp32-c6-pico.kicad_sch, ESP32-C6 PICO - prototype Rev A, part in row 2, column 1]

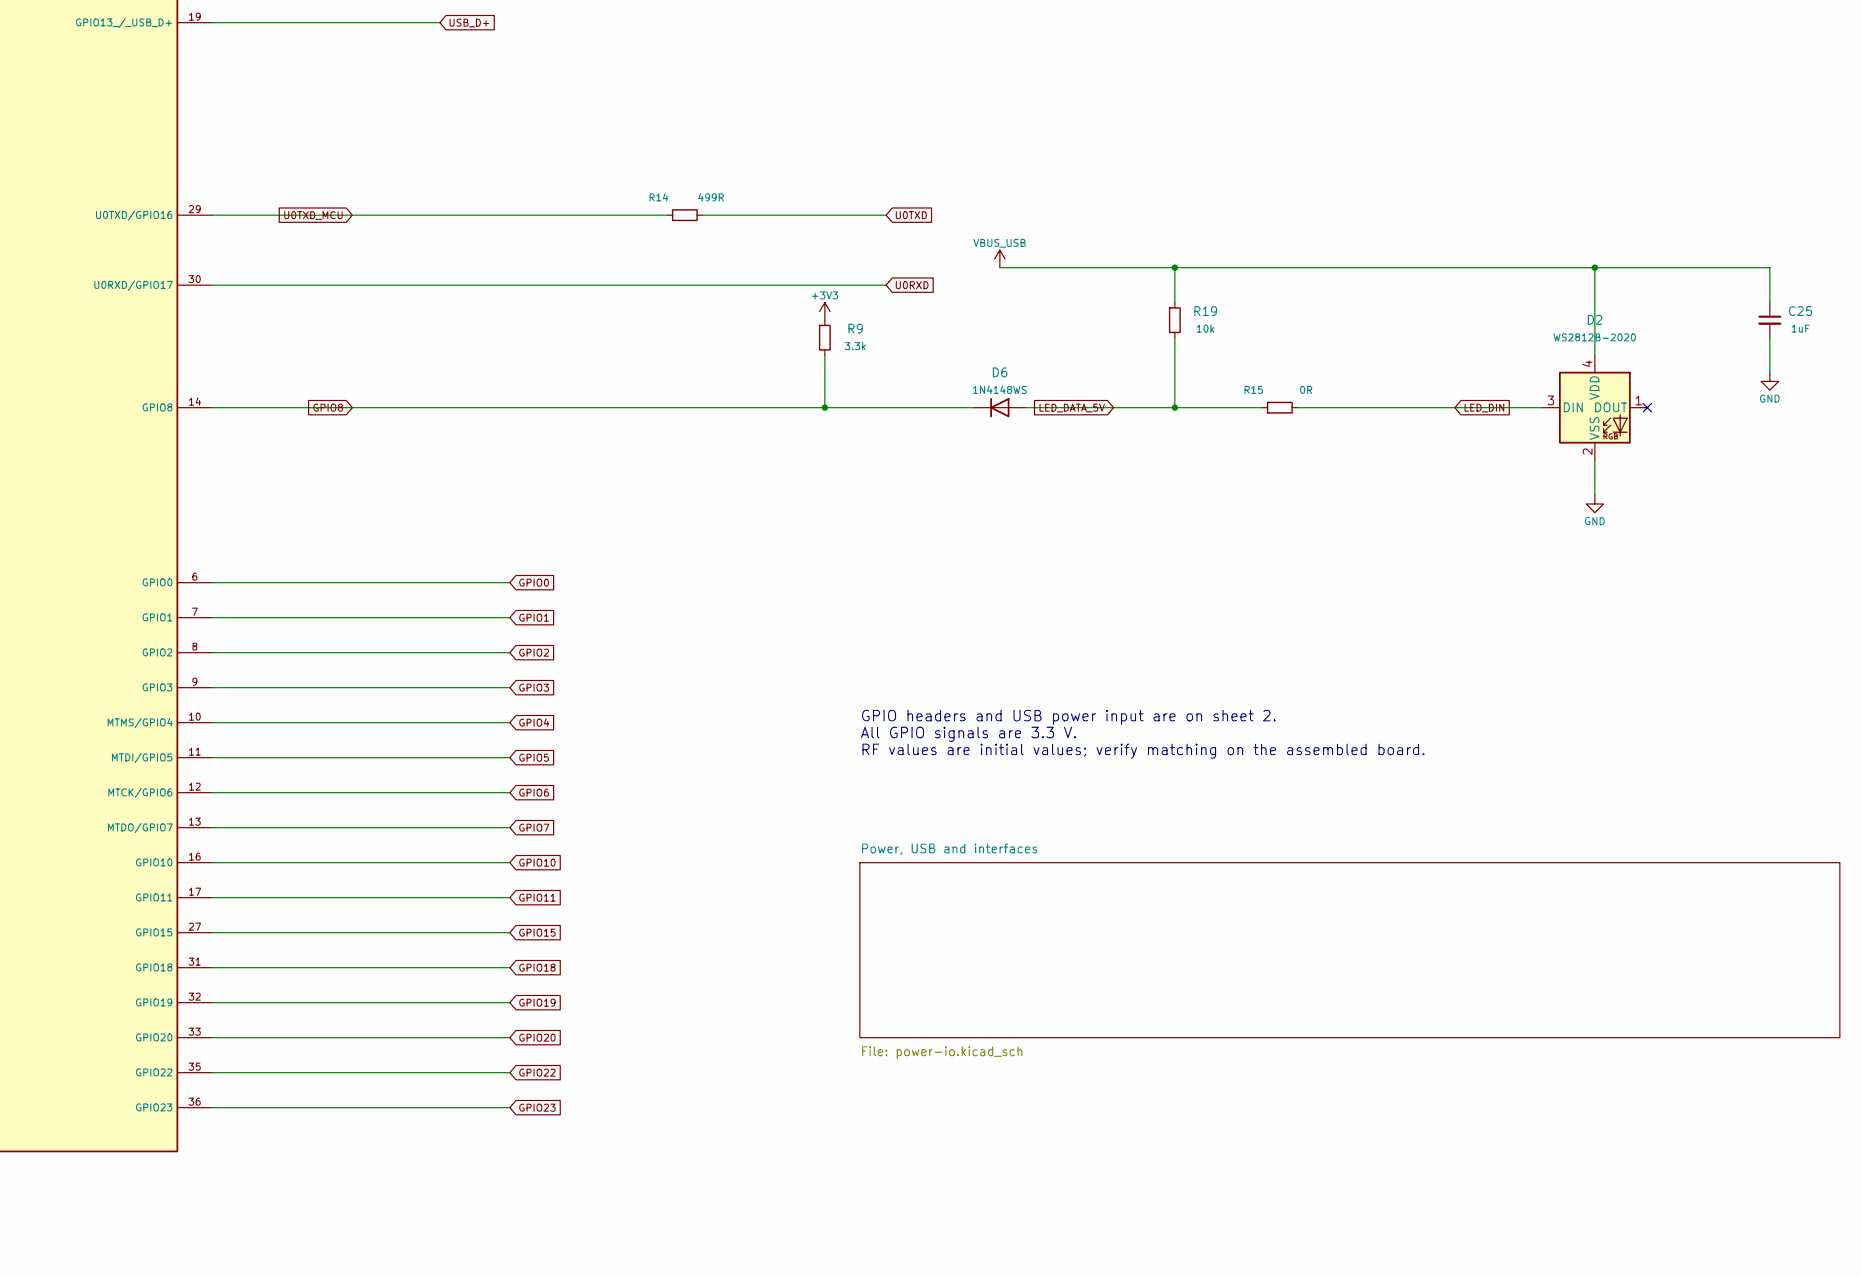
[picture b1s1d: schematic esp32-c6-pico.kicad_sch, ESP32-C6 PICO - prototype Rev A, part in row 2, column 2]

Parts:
AE1: RFANT5220110A0T; MPN RFANT5220110A0T
C2, C3: 1.5pF; C_0201_0603Metric; MPN 1.5pF
C4, C5: 12pF; C_0402_1005Metric; MPN 12pF
C6, C10, C12, C13, C14, C15: 100nF; C_0402_1005Metric; MPN 100nF
C7, C9, C11, C21, C25: 1uF; C_0402_1005Metric; MPN 1uF
C8, C19, C20: 10uF; C_0402_1005Metric; MPN 10uF
C16: 10pF; C_0201_0603Metric; MPN 10pF
C17, C18: DNP; C_0201_0603Metric; MPN DNP; not fitted
D1: PESD5V0F1BL-Q; D_SOD-882; MPN PESD5V0F1BL-Q; not fitted
D2: WS2812B-2020; LED_WS2812B-2020_PLCC4_2.0x2.0mm; MPN WS2812B-2020
D6: 1N4148WS; D_SOD-323; MPN 1N4148WS-7-F
L1: 2.4nH; L_0201_0603Metric; MPN 2.4nH
L2: 2.0nH; L_0402_1005Metric; MPN 2.0nH
L3: DNP; L_0201_0603Metric; MPN DNP; not fitted
R1, R2, R3, R4, R5, R15, R17, R18: 0R; R_0402_1005Metric; MPN 0R
R6: 0R; R_0201_0603Metric; MPN 0R
R7, R8, R19: 10k; R_0402_1005Metric; MPN 10k
R9: 3.3k; R_0402_1005Metric; MPN 3.3k
R14: 499R; R_0402_1005Metric; MPN 499R
SW1: RESET; SW_Push_1P1T_NO_CK_KMR2; MPN KMR221GLFS
SW2: BOOT; SW_Push_1P1T_NO_CK_KMR2; MPN KMR221GLFS
U1: ESP32-C6; QFN40_ESP32_C6_Compact; MPN ESP32-C6
U3: W25Q32JVSNIQ; SOIC-8_3.9x4.9mm_P1.27mm; MPN W25Q32JVSNIQ
Y1: 40MHz / CL=8pF; Crystal_SMD_2016-4Pin_2.0x1.6mm; MPN E9X400081G08

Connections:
+3V3: C8.1, C9.1, C10.1, C12.1, C13.1, C14.1, C15.1, L2.1, R7.1, R8.1, R9.1, U1.5 (VDDPST1), U1.28 (VDDPST2), U1.37 (VDDA1), U1.40 (VDDA2); also elsewhere on the board
ANT_FEED: AE1.1 (FEED_1), C18.1, D1.2 (A2), R6.2
CHIP_EN: C21.1, R7.2, SW1.1, U1.4 (CHIP_PU_/_EN)
GND: C2.2, C3.2, C4.2, C5.2, C6.2, C7.2, C8.2, C9.2, C10.2, C11.2, C12.2, C13.2, C14.2, C15.2, C17.2, C18.2, C19.2, C20.2, C21.2, C25.2, D1.1 (A1), D2.2 (VSS), L3.2, SW1.2, SW2.2, U1.41 (GND), U3.4 (GND), Y1.2 (G), Y1.4 (G); also elsewhere on the board
GPIO0: U1.6 (GPIO0); also elsewhere on the board
GPIO1: U1.7 (GPIO1); also elsewhere on the board
GPIO2: U1.8 (GPIO2); also elsewhere on the board
GPIO3: U1.9 (GPIO3); also elsewhere on the board
GPIO4: U1.10 (MTMS/GPIO4); also elsewhere on the board
GPIO5: U1.11 (MTDI/GPIO5); also elsewhere on the board
GPIO6: U1.12 (MTCK/GPIO6); also elsewhere on the board
GPIO7: U1.13 (MTDO/GPIO7); also elsewhere on the board
GPIO8: D6.1 (K), R9.2, U1.14 (GPIO8)
GPIO9_BOOT: R8.2, SW2.1, U1.15 (GPIO9); also elsewhere on the board
GPIO10: U1.16 (GPIO10); also elsewhere on the board
GPIO11: U1.17 (GPIO11); also elsewhere on the board
GPIO15: U1.27 (GPIO15); also elsewhere on the board
GPIO18: U1.31 (GPIO18); also elsewhere on the board
GPIO19: U1.32 (GPIO19); also elsewhere on the board
GPIO20: U1.33 (GPIO20); also elsewhere on the board
GPIO21: U1.34 (GPIO21); also elsewhere on the board
GPIO22: U1.35 (GPIO22); also elsewhere on the board
GPIO23: U1.36 (GPIO23); also elsewhere on the board
LED_DATA_5V: D6.2 (A), R15.1, R19.2
LED_DIN: D2.3 (DIN), R15.2
RF_50: C16.2, C17.1, L3.1, R6.1
RF_CHIP: C3.1, L1.1, U1.1 (ANT)
RF_MID: C2.1, C16.1, L1.2
SPI_CLK: R4.2, U3.6 (CLK)
SPI_CLK_MCU: R4.1, U1.25 (SPICLK/GPIO29)
SPI_CS: R17.2, U3.1 (~CS)
SPI_CS_MCU: R17.1, U1.20 (SPICS0/GPIO24)
SPI_D: R5.2, U3.5 (DI_/_IO0)
SPI_D_MCU: R5.1, U1.26 (SPID/GPIO30)
SPI_HD: R3.2, U3.7 (~HOLD_/_IO3)
SPI_HD_MCU: R3.1, U1.24 (SPIHD/GPIO28)
SPI_Q: R1.2, U3.2 (DO_/_IO1)
SPI_Q_MCU: R1.1, U1.21 (SPIQ/GPIO25)
SPI_WP: R2.2, U3.3 (~WP_/_IO2)
SPI_WP_MCU: R2.1, U1.22 (SPIWP/GPIO26)
U0RXD: U1.30 (U0RXD/GPIO17); also elsewhere on the board
U0TXD: R14.2; also elsewhere on the board
U0TXD_MCU: R14.1, U1.29 (U0TXD/GPIO16)
USB_D+: U1.19 (GPIO13_/_USB_D+); also elsewhere on the board
USB_D-: U1.18 (GPIO12_/_USB_D-); also elsewhere on the board
V3A: C11.1, C19.1, C20.1, L2.2, U1.2 (VDDA3P3), U1.3 (VDDA3P3)
VBUS_USB: C25.1, D2.4 (VDD), R19.1; also elsewhere on the board
VDD_SPI: C6.1, C7.1, U1.23 (VDD_SPI), U3.8 (VCC)
XTAL_LOAD_P: C4.1, R18.2, Y1.1
XTAL_N: C5.1, U1.38 (XTAL_N), Y1.3
XTAL_P: R18.1, U1.39 (XTAL_P)

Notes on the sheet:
3V3 bulk and VDDA3P3 filtering
Native USB Serial/JTAG / connector and TVS on sheet 2
ESP32-C6 PICO | DIRECT-WIRED PERIPHERALS | REV A
40 MHz crystal / local load capacitors
GPIO headers and USB power input are on sheet 2. All GPIO signals are 3.3 V. RF values are initial values; verify matching on the assembled board.
BOOT: GPIO8 high, GPIO9 low at reset
RF matching / 0201 unchanged
4 MB QSPI flash / series resistors at U1
EN delay and RESET

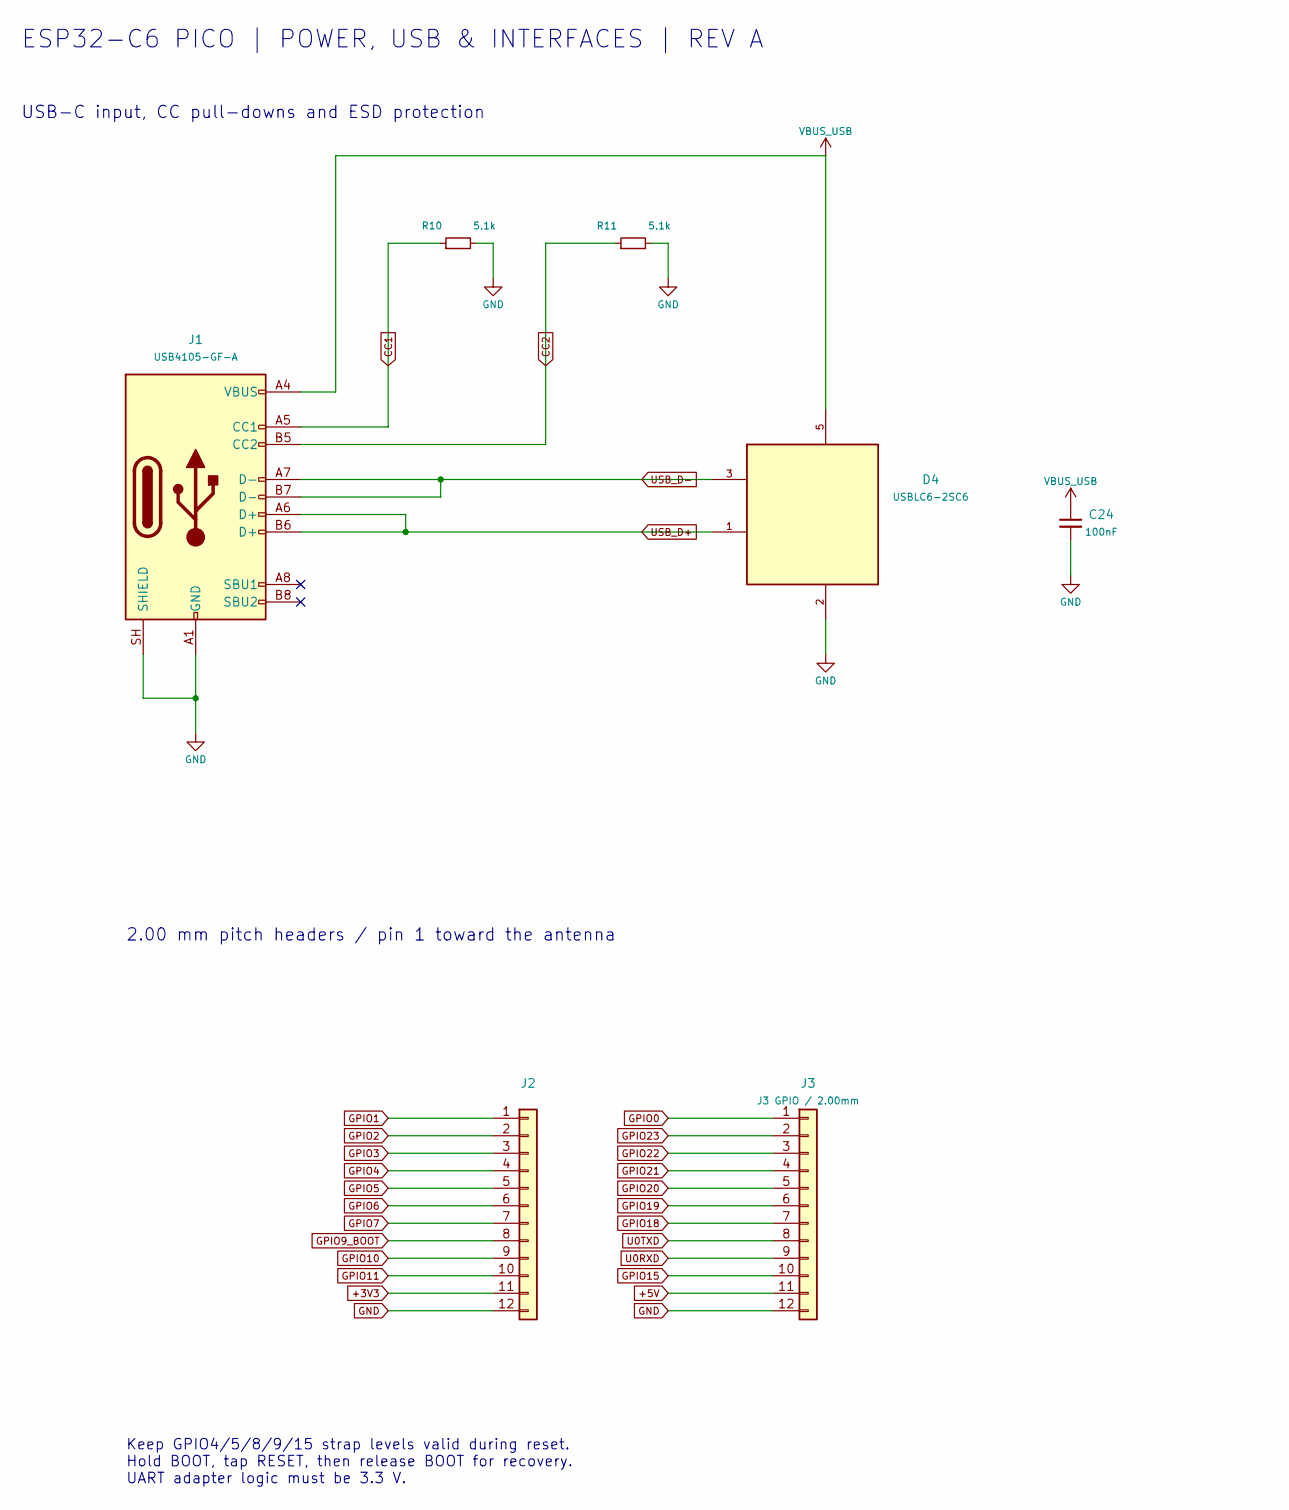
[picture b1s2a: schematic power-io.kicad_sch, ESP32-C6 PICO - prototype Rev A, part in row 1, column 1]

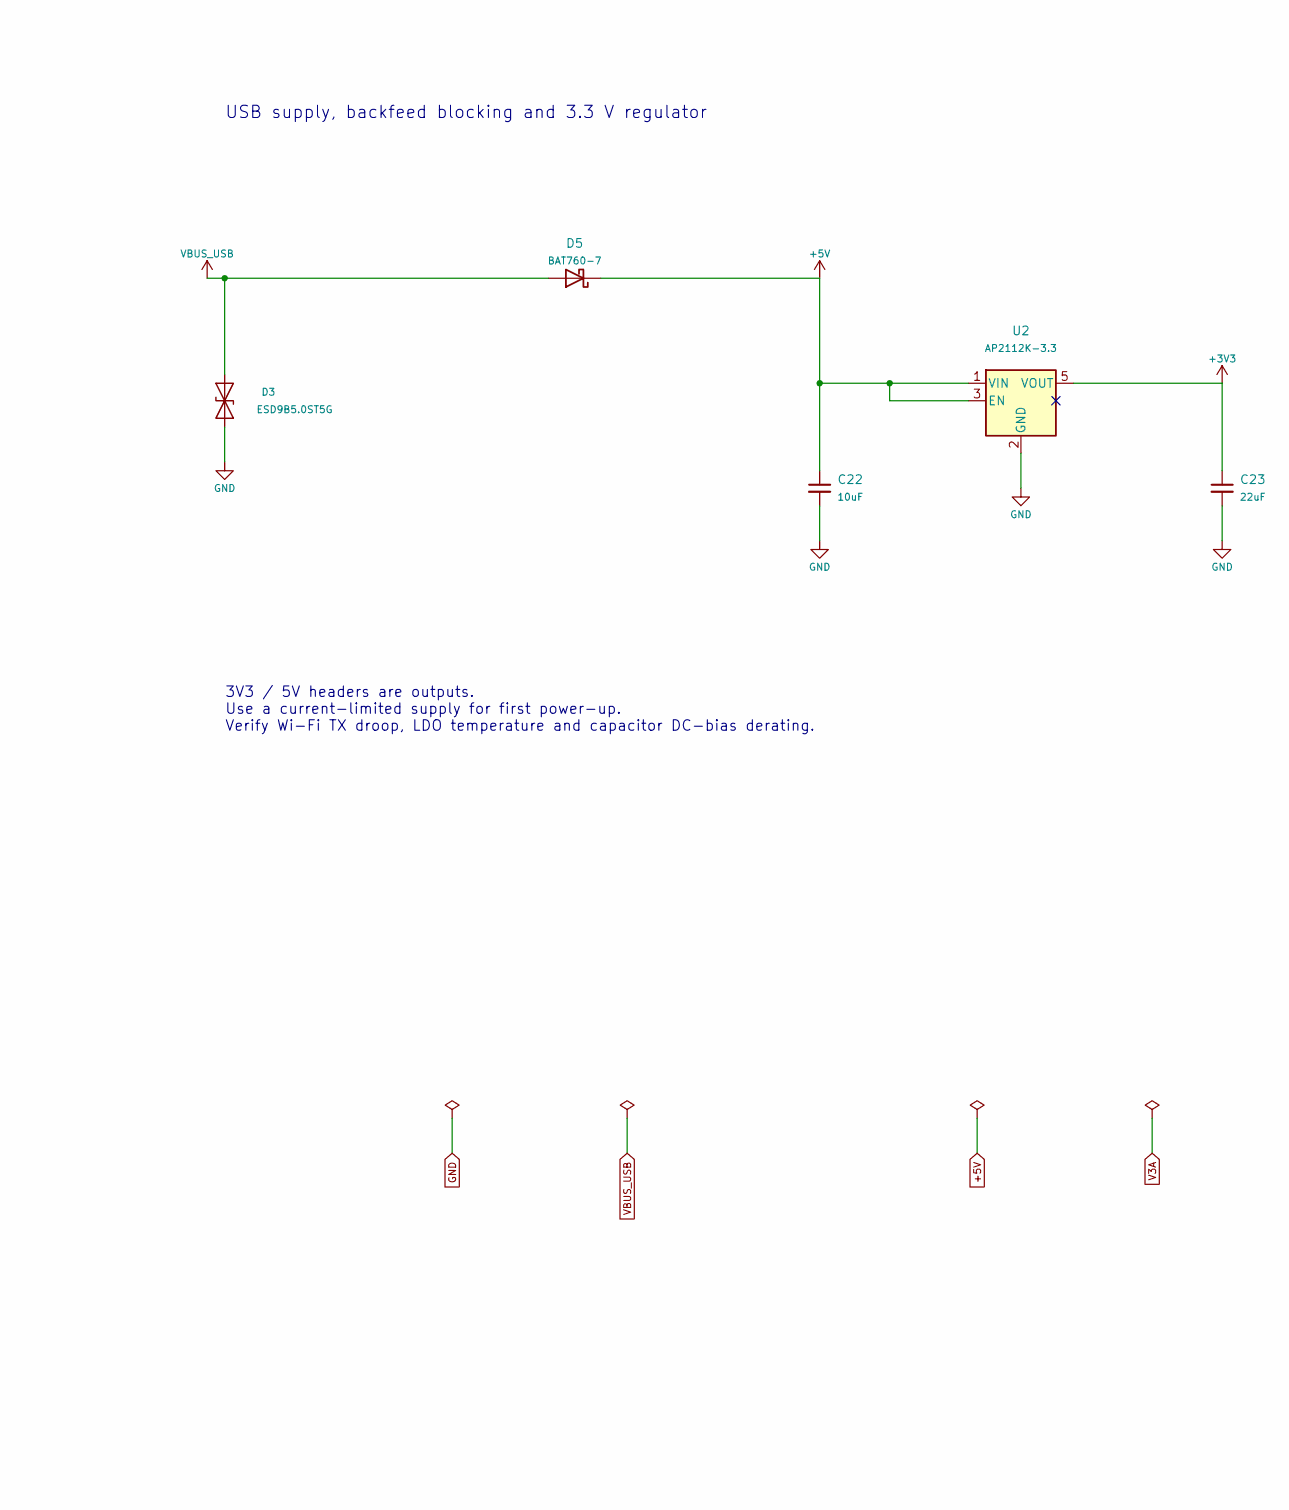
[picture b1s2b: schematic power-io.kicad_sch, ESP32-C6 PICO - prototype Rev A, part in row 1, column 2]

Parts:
C22: 10uF; C_0402_1005Metric; MPN 10uF
C23: 22uF; C_0402_1005Metric; MPN 22uF
C24: 100nF; C_0402_1005Metric; MPN 100nF
D3: ESD9B5.0ST5G; D_SOD-923; MPN ESD9B5.0ST5G
D4: USBLC6-2SC6; SOT-23-6; MPN USBLC6-2SC6
D5: BAT760-7; D_SOD-323; MPN BAT760-7
J1: USB4105-GF-A; USB_C_Receptacle_GCT_USB4105-xx-A_16P_TopMnt_Horizontal; MPN USB4105-GF-A
J2: J2 GPIO / 2.00mm; PinHeader_1x12_P2.00mm_Compact; MPN 1x12 P2.00 vertical header
J3: J3 GPIO / 2.00mm; PinHeader_1x12_P2.00mm_Compact; MPN 1x12 P2.00 vertical header
R10, R11: 5.1k; R_0402_1005Metric; MPN 5.1k
U2: AP2112K-3.3; SOT-23-5; MPN AP2112K-3.3TRG1

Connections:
+3V3: C23.1, J2.11, U2.5 (VOUT); also elsewhere on the board
+5V: C22.1, D5.1 (K), J3.11, U2.1 (VIN), U2.3 (EN)
CC1: J1.A5 (CC1), R10.1
CC2: J1.B5 (CC2), R11.1
GND: C22.2, C23.2, C24.2, D3.1 (A1), D4.2 (GND), J1.A1 (GND), J1.A12 (GND), J1.B1 (GND), J1.B12 (GND), J1.SH (SHIELD), J2.12, J3.12, R10.2, R11.2, U2.2 (GND); also elsewhere on the board
GPIO0: J3.1; also elsewhere on the board
GPIO1: J2.1; also elsewhere on the board
GPIO2: J2.2; also elsewhere on the board
GPIO3: J2.3; also elsewhere on the board
GPIO4: J2.4; also elsewhere on the board
GPIO5: J2.5; also elsewhere on the board
GPIO6: J2.6; also elsewhere on the board
GPIO7: J2.7; also elsewhere on the board
GPIO9_BOOT: J2.8; also elsewhere on the board
GPIO10: J2.9; also elsewhere on the board
GPIO11: J2.10; also elsewhere on the board
GPIO15: J3.10; also elsewhere on the board
GPIO18: J3.7; also elsewhere on the board
GPIO19: J3.6; also elsewhere on the board
GPIO20: J3.5; also elsewhere on the board
GPIO21: J3.4; also elsewhere on the board
GPIO22: J3.3; also elsewhere on the board
GPIO23: J3.2; also elsewhere on the board
U0RXD: J3.9; also elsewhere on the board
U0TXD: J3.8; also elsewhere on the board
USB_D+: D4.1 (D+_(1,6)), D4.6 (D+), J1.A6 (D+), J1.B6 (D+); also elsewhere on the board
USB_D-: D4.3 (D-_(3,4)), D4.4 (D-), J1.A7 (D-), J1.B7 (D-); also elsewhere on the board
VBUS_USB: C24.1, D3.2 (A2), D4.5 (VBUS), D5.2 (A), J1.A4 (VBUS), J1.A9 (VBUS), J1.B4 (VBUS), J1.B9 (VBUS); also elsewhere on the board

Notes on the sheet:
ESP32-C6 PICO | POWER, USB & INTERFACES | REV A
USB-C input, CC pull-downs and ESD protection
3V3 / 5V headers are outputs. Use a current-limited supply for first power-up. Verify Wi-Fi TX droop, LDO temperature and capacitor DC-bias derating.
USB supply, backfeed blocking and 3.3 V regulator
2.00 mm pitch headers / pin 1 toward the antenna
Keep GPIO4/5/8/9/15 strap levels valid during reset. Hold BOOT, tap RESET, then release BOOT for recovery. UART adapter logic must be 3.3 V.
